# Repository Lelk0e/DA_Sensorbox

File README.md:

# DA_Sensorbox
Partnerfirma: b2-electronics
Teammitglieder: Mayer Phillip, Yilmaz Mert-Can, Schatzmann Alexander, Marte Linus
Software: Clockify, Github

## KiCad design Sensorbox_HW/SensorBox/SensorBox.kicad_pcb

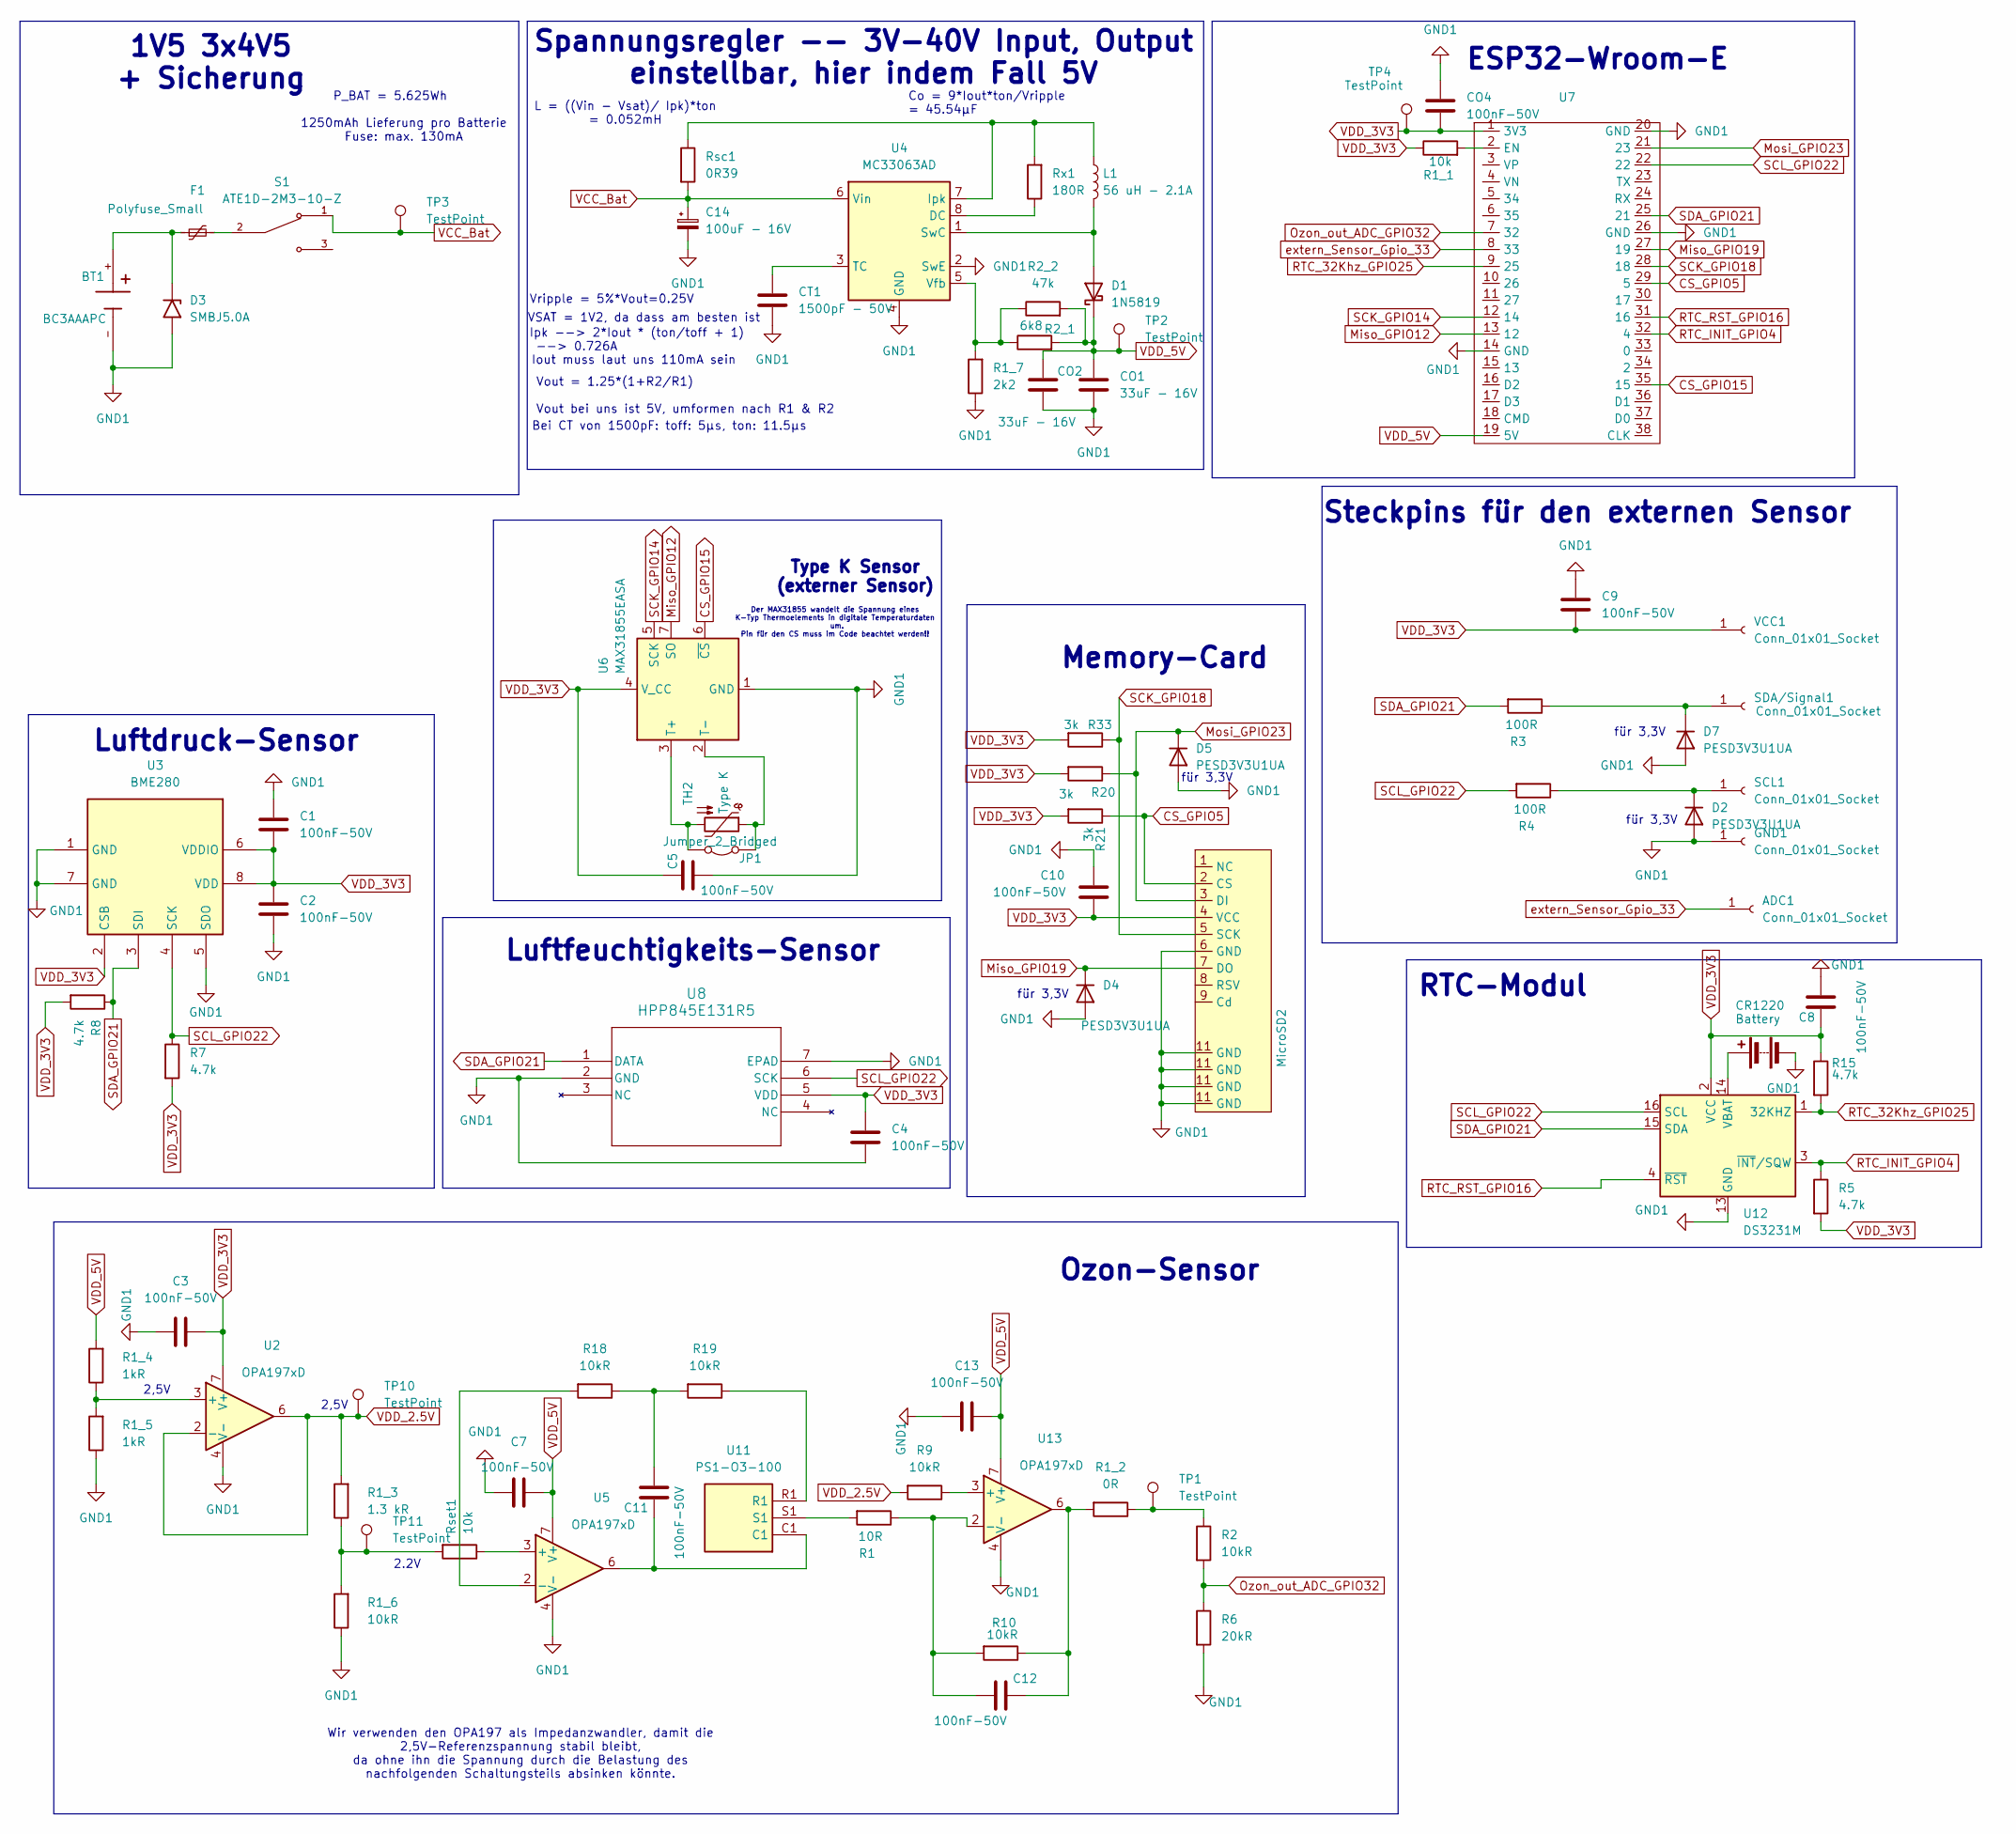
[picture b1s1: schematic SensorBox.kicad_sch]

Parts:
ADC1: Conn_01x01_Socket; PinHeader_1x01_P2.00mm_Vertical
BT1: BC3AAAPC; BatteryHolder_Keystone_2479_3xAAA; PARTREV J
C1, C2, C3, C4, C5, C7, C8, C9, C10, C11, C12, C13: 100nF-50V; C_1206_3216Metric_Pad1.33x1.80mm_HandSolder
C14: 100uF - 16V; CP_Elec_6.3x7.7
CO1, CO2: 33uF - 16V; C_1812_4532Metric_Pad1.57x3.40mm_HandSolder
CO4: 100nF-50V; C_1206_3216Metric_Pad1.33x1.80mm_HandSolder
CR1220: Battery; BatteryHolder_LINX_BAT-HLD-012-SMT
CT1: 1500pF - 50V; C_1206_3216Metric_Pad1.33x1.80mm_HandSolder
D1: 1N5819; D_SMB-SMC_Universal_Handsoldering
D2, D4, D5, D7: PESD3V3U1UA; D_SOD-323
D3: SMBJ5.0A; D_SMB_Handsoldering
F1: Polyfuse_Small; Fuse_Littelfuse_372_D8.50mm
GND1: Conn_01x01_Socket; PinHeader_1x01_P2.00mm_Vertical
JP1: Jumper_2_Bridged; PinHeader_1x02_P2.54mm_Vertical
L1: 56 uH - 2.1A; L1
MicroSD2: microSD_HC_Molex_104031-0811
R1: 10R; R_1206_3216Metric_Pad1.30x1.75mm_HandSolder
R1_1: 10k; R_1206_3216Metric_Pad1.30x1.75mm_HandSolder
R1_2: 0R; R_1206_3216Metric_Pad1.30x1.75mm_HandSolder
R1_3: 1.3 kR; R_1206_3216Metric_Pad1.30x1.75mm_HandSolder
R1_4, R1_5: 1kR; R_1206_3216Metric_Pad1.30x1.75mm_HandSolder
R1_6, R2, R9, R10, R18, R19: 10kR; R_1206_3216Metric_Pad1.30x1.75mm_HandSolder
R1_7: 2k2; R_1206_3216Metric_Pad1.30x1.75mm_HandSolder
R2_1: 6k8; R_1206_3216Metric_Pad1.30x1.75mm_HandSolder
R2_2: 47k; R_1206_3216Metric_Pad1.30x1.75mm_HandSolder
R3, R4: 100R; R_1206_3216Metric_Pad1.30x1.75mm_HandSolder
R5, R7, R8, R15: 4.7k; R_1206_3216Metric_Pad1.30x1.75mm_HandSolder
R6: 20kR; R_1206_3216Metric_Pad1.30x1.75mm_HandSolder
R20, R21, R33: 3k; R_1206_3216Metric_Pad1.30x1.75mm_HandSolder
Rsc1: 0R39; R_1206_3216Metric_Pad1.30x1.75mm_HandSolder
Rset1: 10k; R_1206_3216Metric_Pad1.30x1.75mm_HandSolder
Rx1: 180R; R_1206_3216Metric_Pad1.30x1.75mm_HandSolder
S1: ATE1D-2M3-10-Z; SW_ATE1D-2M3-10-Z
SCL1: Conn_01x01_Socket; PinHeader_1x01_P2.00mm_Vertical
SDA/Signal1: Conn_01x01_Socket; PinHeader_1x01_P2.00mm_Vertical
TH2: Type K; R_Axial_DIN0204_L3.6mm_D1.6mm_P5.08mm_Horizontal
TP1, TP2, TP3, TP4, TP10, TP11: TestPoint; TestPoint_Loop_D1.80mm_Drill1.0mm_Beaded
U2, U5, U13: OPA197xD; SOIC-8_3.9x4.9mm_P1.27mm
U3: BME280; Bosch_LGA-8_2.5x2.5mm_P0.65mm_ClockwisePinNumbering_ch
U4: MC33063AD; SOIC-8_3.9x4.9mm_P1.27mm
U6: MAX31855EASA; SOIC-8_3.9x4.9mm_P1.27mm
U7: ESP32_Wroom_E
U8: HPP845E131R5; SON6_HPP845E131R5_TEC
U11: PS1-O3-100; PS1O3100; Manufacturer_Part_Number PS1-O3-100
U12: DS3231M; SOIC-16W_7.5x10.3mm_P1.27mm
VCC1: Conn_01x01_Socket; PinHeader_1x01_P2.00mm_Vertical

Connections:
CS_GPIO5: MicroSD2.2 (CS), R21.1, U7.29 (5)
CS_GPIO15: U6.6 (~CS), U7.35 (15)
GND1: BT1.-, C1.1, C2.1, C3.2, C4.2, C5.2, C7.2, C8.2, C9.2, C10.2, C13.2, C14.2, CO1.2, CO2.2, CO4.1, CR1220.2 (-), CT1.2, D2.2 (A), D3.2 (A2), D4.2 (A), D5.2 (A), D7.2 (A), GND1.1, MicroSD2.6 (GND), MicroSD2.11 (GND), R1_5.1, R1_6.1, R1_7.1, R6.2, U2.4 (V-), U3.1 (GND), U3.5 (SDO), U3.7 (GND), U4.2 (SwE), U4.4 (GND), U5.4 (V-), U6.1 (GND), U7.14 (GND), U7.20 (GND), U7.26 (GND), U8.2 (GND), U8.7 (EPAD), U12.5 (GND), U12.6 (GND), U12.7 (GND), U12.8 (GND), U12.9 (GND), U12.10 (GND), U12.11 (GND), U12.12 (GND), U12.13 (GND), U13.4 (V-)
Miso_GPIO12: U6.7 (SO), U7.13 (12)
Miso_GPIO19: D4.1 (K), MicroSD2.7 (DO), U7.27 (19)
Mosi_GPIO23: D5.1 (K), MicroSD2.3 (DI), R20.1, U7.21 (23)
unnamed: C11.1, U5.6, U11.C1
unnamed: C11.2, R18.1, R19.2
unnamed: C12.2, R1_2.2, R10.1, U13.6
unnamed: CR1220.1 (+), U12.14 (VBAT)
unnamed: D1.2 (A), L1.2, U4.1 (SwC)
unnamed: D2.1 (K), R4.1, SCL1.1
unnamed: BT1.+, D3.1 (A1), F1.1
unnamed: D7.1 (K), R3.1, SDA/Signal1.1
unnamed: F1.2, S1.2
unnamed: JP1.1 (A), TH2.1, U6.2 (T-)
unnamed: JP1.2 (B), TH2.2, U6.3 (T+)
unnamed: R1.2, U11.S1
unnamed: R1_2.1, R2.1, TP1.1
unnamed: R1_3.1, R1_6.2, Rset1.2, TP11.1
unnamed: R19.1, U11.R1
unnamed: R1_4.1, R1_5.2, U2.3 (+)
unnamed: Rx1.1, U4.8 (DC)
unnamed: L1.1, Rsc1.1, Rx1.2, U4.7 (Ipk)
unnamed: CT1.1, U4.3 (TC)
unnamed: R1_7.2, R2_1.1, R2_2.1, U4.5 (Vfb)
unnamed: Rset1.1, U5.3 (+)
unnamed: R18.2, U5.2 (-)
unnamed: R1_1.2, U7.2 (EN)
unnamed: R9.1, U13.3 (+)
unnamed: C12.1, R1.1, R10.2, U13.2 (-)
Ozon_out_ADC_GPIO32: R2.2, R6.1, U7.7 (32)
RTC_32Khz_GPIO25: R15.2, U7.9 (25), U12.1 (32KHZ)
RTC_INIT_GPIO4: R5.1, U7.32 (4), U12.3 (~INT/SQW)
RTC_RST_GPIO16: U7.31 (16), U12.4 (~RST)
SCK_GPIO14: U6.5 (SCK), U7.12 (14)
SCK_GPIO18: MicroSD2.5 (SCK), R33.1, U7.28 (18)
SCL_GPIO22: R4.2, R7.1, U3.4 (SCK), U7.22, U8.6 (SCK), U12.16 (SCL)
SDA_GPIO21: R3.2, R8.1, U3.3 (SDI), U7.25 (21), U8.1 (DATA), U12.15 (SDA)
VCC_Bat: C14.1, Rsc1.2, S1.1, TP3.1, U4.6 (Vin)
VDD_2.5V: R1_3.2, R9.2, TP10.1, U2.2 (-), U2.6
VDD_3V3: C1.2, C2.2, C3.1, C4.1, C5.1, C8.1, C9.1, C10.1, CO4.2, MicroSD2.4 (VCC), R1_1.1, R5.2, R7.2, R8.2, R15.1, R20.2, R21.2, R33.2, TP4.1, U2.7 (V+), U3.2 (CSB), U3.6 (VDDIO), U3.8 (VDD), U6.4 (V_CC), U7.1 (3V3), U8.5 (VDD), U12.2 (VCC), VCC1.1
VDD_5V: C7.1, C13.1, CO1.1, CO2.1, D1.1 (K), R1_4.2, R2_1.2, R2_2.2, TP2.1, U5.7 (V+), U7.19 (5V), U13.7 (V+)
extern_Sensor_Gpio_33: ADC1.1, U7.8 (33)

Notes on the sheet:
für 3,3V
Luftdruck-Sensor
Vripple = 5%*Vout=0.25V
Spannungsregler -- 3V-40V Input, Output einstellbar, hier indem Fall 5V
Luftfeuchtigkeits-Sensor
Ipk --> 2*Iout * (ton/toff + 1) --> 0.726A
Type K Sensor (externer Sensor)
Steckpins für den externen Sensor
1V5 3x4V5 + Sicherung
Memory-Card
Bei CT von 1500pF: toff: 5µs, ton: 11.5µs
Iout muss laut uns 110mA sein
ESP32-Wroom-E
Der MAX31855 wandelt die Spannung eines K-Typ Thermoelements in digitale Temperaturdaten um. Pin für den CS muss im Code beachtet werden!!
RTC-Modul
Wir verwenden den OPA197 als Impedanzwandler, damit die 2,5V-Referenzspannung stabil bleibt, da ohne ihn die Spannung durch die Belastung des nachfolgenden Schaltungsteils absinken könnte.
VSAT = 1V2, da dass am besten ist
1250mAh Lieferung pro Batterie Fuse: max. 130mA
Co = 9*Iout*ton/Vripple = 45.54µF
Vout = 1.25*(1+R2/R1) Vout bei uns ist 5V, umformen nach R1 & R2
P_BAT = 5.625Wh
L = ((Vin - Vsat)/ Ipk)*ton = 0.052mH
2,5V
Ozon-Sensor
2.2V

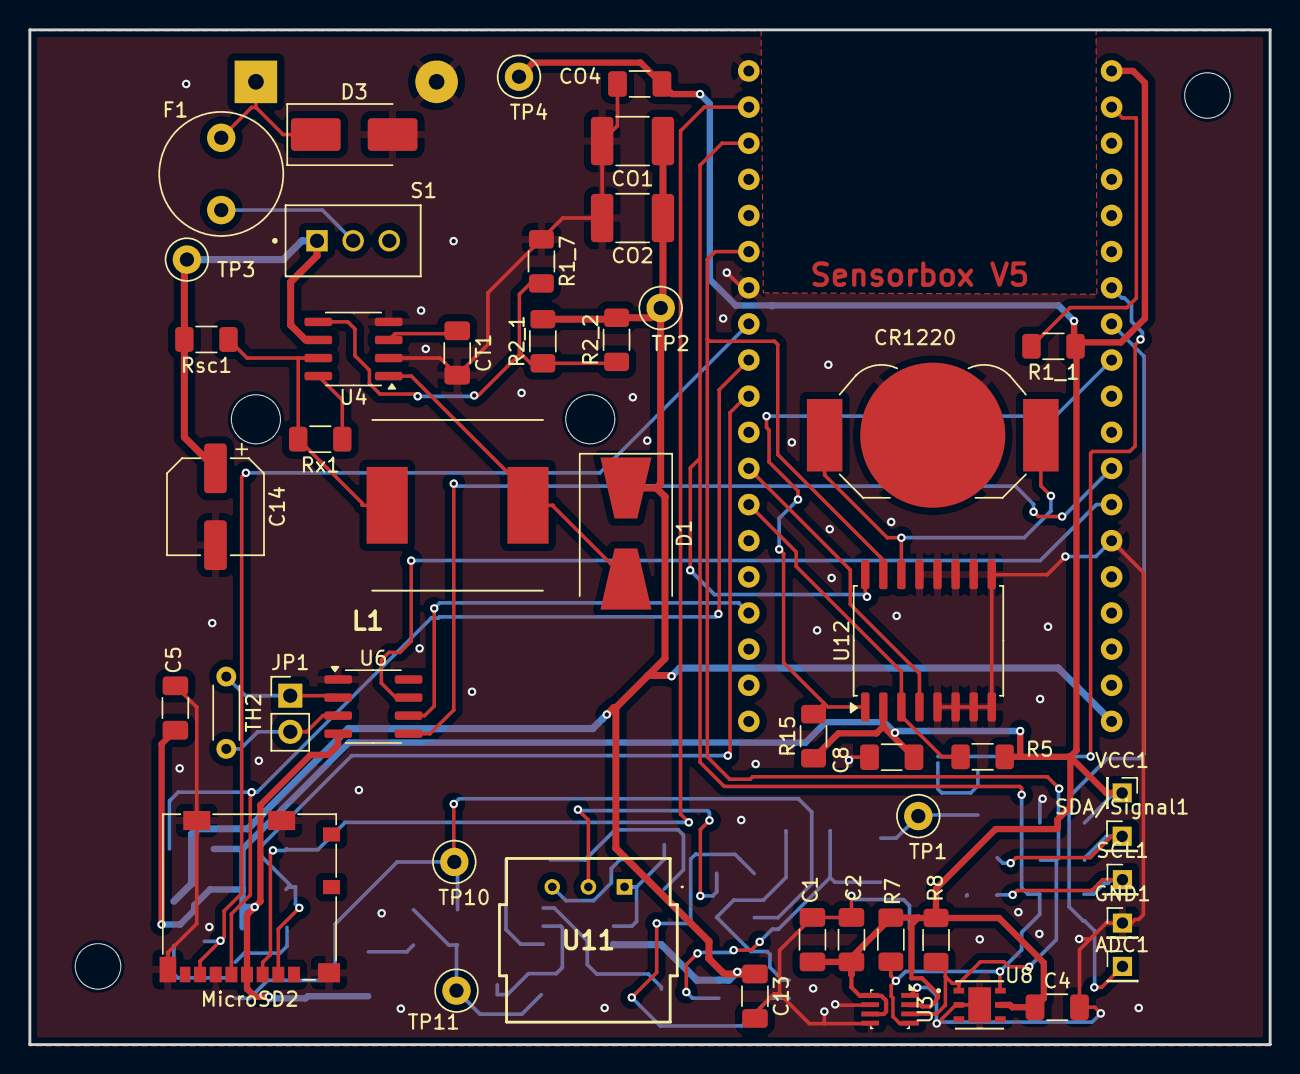
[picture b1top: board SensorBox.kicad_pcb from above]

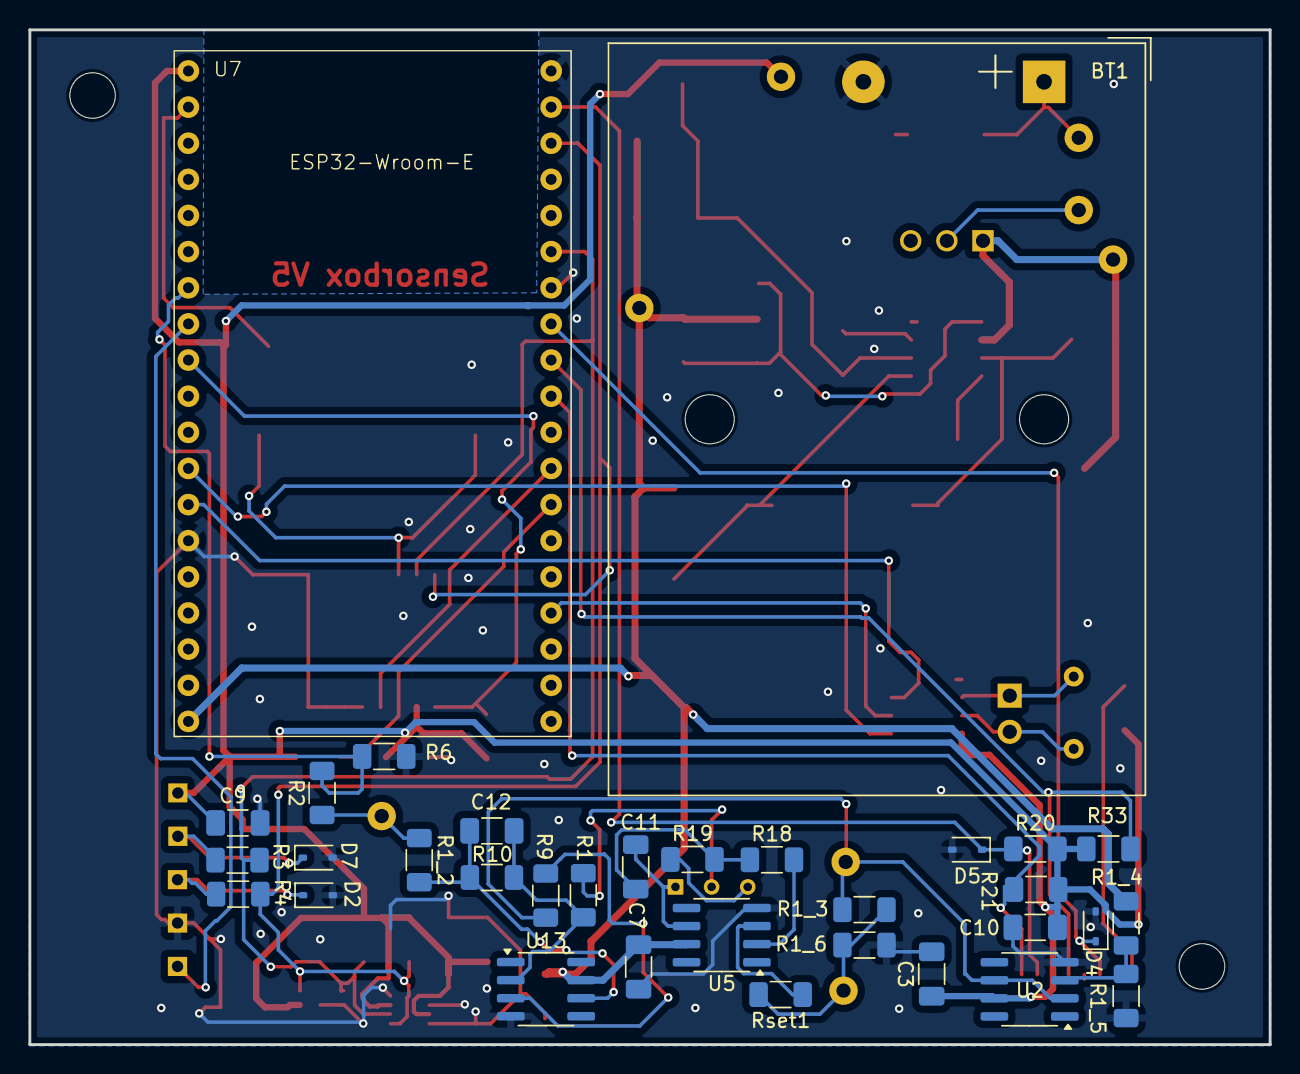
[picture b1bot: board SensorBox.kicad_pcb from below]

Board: 2 copper layers, 87.2 x 71.3 mm, 80 parts (33 on the bottom side), 44 nets.

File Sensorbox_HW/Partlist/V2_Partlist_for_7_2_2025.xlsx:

HW-SENSORBOX
Bauteilnamen | Werte | Datasheet | Footprint | Anzahl für 1 Sensorbox | Anzahl für 4 Sensorboxen | Bestellnummer | Besteller | Link
ADC1,GND1,SCL1,SDA/Signal1,VCC1 | Conn_01x01_Socket | ~ | Connector_PinHeader_2.00mm:PinHeader_1x01_P2.00mm_Vertical | 5 | 10 | BCS-105-L-S-TE | Mouser | https://www.mouser.at/ProductDetail/Samtec/BCS-105-L-S-TE?qs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
BT1 | BC3AAAPC |  | Battery_Basket:BatteryHolder_Keystone_2479_3xAAA | 1 | 10 | BC4AAAPC-ND | Digikey | https://www.digikey.com/en/products/detail/mpd-memory-protec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
C1,C2,C3,C4,C5,C7,C8,C9,C10,C11,C12,C13,CO4 | 100nF-50V | ~ | Capacitor_SMD:C_1206_3216Metric_Pad1.33x1.80mm_HandSolder | 13 | 130 | VJ1206Y104JXAAT | Mouser | https://www.mouser.at/ProductDetail/Vishay-Vitramon/VJ1206Y1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
C14 - GEPOLT | 100uF - 16V | ~ | Capacitor_SMD:CP_Elec_6.3x7.7 | 1 | 10 | AVS107M16E16T-F | Mouser | https://www.mouser.at/ProductDetail/Cornell-Dubilier-CDE/AVS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
CO1,CO2 | 33uF - 16V | ~ | Capacitor_SMD:C_1812_4532Metric_Pad1.57x3.40mm_HandSolder | 2 | 20 | C4532X5R1C336M250KA | Mouser | https://www.mouser.at/ProductDetail/TDK/C4532X5R1C336M250KA?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
CR1220 | Battery | ~ | Battery:BatteryHolder_LINX_BAT-HLD-012-SMT | 1 | 10 | BAT-HLD-012-SMT | Mouser | https://eu.mouser.com/ProductDetail/TE-Connectivity-Linx-Tec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
CT1 | 1500pF - 50V | ~ | Capacitor_SMD:C_1206_3216Metric_Pad1.33x1.80mm_HandSolder | 1 | 10 | VJ1206A152JXAMT | Mouser | https://www.mouser.at/ProductDetail/Vishay-Vitramon/VJ1206A1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
D1 | 1N5819 | http://www.vishay.com/docs/88525/1n5817.pdf | Diode_SMD:D_SMB-SMC_Universal_Handsoldering | 1 | 10 | 1N5819HW-7-F | Mouser | https://www.mouser.at/ProductDetail/Diodes-Incorporated/1N58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
D2,D4,D5,D7 | PESD3V3U1UA | https://www.vishay.com/docs/85751/1n4148ws.pdf | Diode_SMD:D_SOD-323 | 4 | 40 | PESD3V3U1UA,115 | Mouser | https://www.mouser.at/ProductDetail/Nexperia/PESD3V3U1UA115?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
D3 | SMBJ5.0A | https://www.vishay.com/docs/88301/15ke.pdf | Diode_SMD:D_SMB_Handsoldering | 1 | 10 | SMBJ5.0A-E3/52 | Mouser | https://www.mouser.at/ProductDetail/Vishay-General-Semicondu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
F1 | Polyfuse_Small | ~ | Fuse:Fuse_Littelfuse_372_D8.50mm | 1 | 10 | LVR016K | Mouser | https://www.mouser.at/ProductDetail/Littelfuse/LVR016K?qs=sG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
JP1 | Jumper_2_Bridged | ~ | Connector_PinHeader_2.54mm:PinHeader_1x02_P2.54mm_Vertical | 1 | 10 | 61300211121 | Mouser | https://www.mouser.at/ProductDetail/Wurth-Elektronik/6130021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
L1 | 56ÂµH - 2.1A | ~ | Inductor_SMD:L_0805_2012Metric_Pad1.05x1.20mm_HandSolder | 1 | 10 | 744771156 | Mouser | https://www.mouser.at/ProductDetail/Wurth-Elektronik/7447711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
MicroSD2,U7 | ~ |  | -- mixed values -- | 2 | 10 | 104031-0811 | Mouser | https://www.mouser.at/ProductDetail/Molex/104031-0811?qs=uds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
R1 | 10R | ~ | Resistor_SMD:R_1206_3216Metric_Pad1.30x1.75mm_HandSolder | 1 | 10 | TNPW120610R0BEEA | Mouser | https://www.mouser.at/ProductDetail/Vishay-Dale/TNPW120610R0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
R1_1,Rset1 | 10k | ~ | Resistor_SMD:R_1206_3216Metric_Pad1.30x1.75mm_HandSolder | 2 | 20 | RT1206FRE1310KL | Mouser | https://www.mouser.at/ProductDetail/YAGEO/RT1206FRE1310KL?qs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
R1_2 | 0R | ~ | Resistor_SMD:R_1206_3216Metric_Pad1.30x1.75mm_HandSolder | 1 | 10 | MCA12060Z0000ZP500 | Mouser | https://www.mouser.at/ProductDetail/Vishay-Beyschlag/MCA1206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
R1_3 | 1.3 kR | ~ | Resistor_SMD:R_1206_3216Metric_Pad1.30x1.75mm_HandSolder | 1 | 10 | CRCW12061K30FKEAHP | Mouser | https://www.mouser.at/ProductDetail/Vishay-Dale/CRCW12061K30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
R1_4,R1_5 | 1kR | ~ | Resistor_SMD:R_1206_3216Metric_Pad1.30x1.75mm_HandSolder | 2 | 20 | ERA-8AEB102V | Mouser | https://www.mouser.at/ProductDetail/Panasonic/ERA-8AEB102V?q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
R1_6,R2,R9,R10,R18,R19 | 10kR | ~ | Resistor_SMD:R_1206_3216Metric_Pad1.30x1.75mm_HandSolder | 6 | 60 | ERA-8VRB1002V | Mouser | https://www.mouser.at/ProductDetail/Panasonic/ERA-8VRB1002V?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
R1_7 | 2k2 | ~ | Resistor_SMD:R_1206_3216Metric_Pad1.30x1.75mm_HandSolder | 1 | 10 | ERJ-T08J222V | Mouser | https://www.mouser.at/ProductDetail/Panasonic/ERJ-T08J222V?q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
R2_1 | 6k8 | ~ | Resistor_SMD:R_1206_3216Metric_Pad1.30x1.75mm_HandSolder | 1 | 10 | MCA12060D6801BP500 | Mouser | https://www.mouser.at/ProductDetail/Vishay-Beyschlag/MCA1206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
R3,R4 | 100R | ~ | Resistor_SMD:R_1206_3216Metric_Pad1.30x1.75mm_HandSolder | 2 | 20 | RT1206FRE13100RL | Mouser | https://www.mouser.at/ProductDetail/YAGEO/RT1206FRE13100RL?q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
R5,R7,R8,R15 | 4.7k | ~ | Resistor_SMD:R_1206_3216Metric_Pad1.30x1.75mm_HandSolder | 4 | 40 | RT1206FRE074K7L | Mouser | https://www.mouser.at/ProductDetail/YAGEO/RT1206FRE074K7L?qs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
R6 | 20kR | ~ | Resistor_SMD:R_1206_3216Metric_Pad1.30x1.75mm_HandSolder | 1 | 10 | ERA-8APB203V | Mouser | https://www.mouser.at/ProductDetail/Panasonic/ERA-8APB203V?q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
R20,R21,R33 | 3k | ~ | Resistor_SMD:R_1206_3216Metric_Pad1.30x1.75mm_HandSolder | 3 | 30 | RT1206FRE073KL | Mouser | https://www.mouser.at/ProductDetail/YAGEO/RT1206FRE073KL?qs=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
Rsc1 | 0R39 | ~ | Resistor_SMD:R_1206_3216Metric_Pad1.30x1.75mm_HandSolder | 1 | 10 | RCWE1206R390FKEA | Mouser | https://www.mouser.at/ProductDetail/Vishay-Dale/RCWE1206R390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
Rx1 | 180R | ~ | Resistor_SMD:R_1206_3216Metric_Pad1.30x1.75mm_HandSolder | 1 | 10 | TNPW1206180RBEEA | Mouser | https://www.mouser.at/ProductDetail/Vishay-Dale/TNPW1206180R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
TH2 | Type K | https://www.heraeus.com/media/media/group/doc_group/products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 | Resistor_THT:R_Axial_DIN0204_L3.6mm_D1.6mm_P5.08mm_Horizontal | 0 | 0 | Type K, PTFE, 1m | x | x
TP1,TP2,TP3,TP4,TP5,TP6,TP7,TP10,TP11 | TestPoint | ~ | TestPoint:TestPoint_Loop_D1.80mm_Drill1.0mm_Beaded | 9 | 100 | SMC-1-01-1-GT | Digikey | https://www.digikey.com/en/products/detail/adam-tech/SMC-1-0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
U1 | BME280 | https://www.bosch-sensortec.com/media/boschsensortec/downloa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 | BME280 (2):BME280 | 0 | 0 | x | x | x
U2,U5,U13 | OPA197xD | http://www.ti.com/lit/ds/symlink/opa197.pdf | Package_SO:SOIC-8_3.9x4.9mm_P1.27mm | 3 | 30 | OPA197IDR | Mouser | https://www.mouser.at/ProductDetail/Texas-Instruments/OPA197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
U4 | MC33063AD | http://www.onsemi.com/pub_link/Collateral/MC34063A-D.PDF | Package_SO:SOIC-8_3.9x4.9mm_P1.27mm | 0 | 0 | x | x | x
U6 | MAX31855EASA | http://datasheets.maximintegrated.com/en/ds/MAX31855.pdf | Package_SO:SOIC-8_3.9x4.9mm_P1.27mm | 1 | 10 | MAX31855EASA+ | Mouser | https://www.mouser.at/ProductDetail/Analog-Devices-Maxim-Int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
U8 | HPP845E131R5 | HPP845E131R5 | HPP_footprints:SON6_HPP845E131R5_TEC | 0 | 0 | x | x | x
U11 | PS1-O3-100 | https://sgx.cdistore.com/datasheets/sgx/ds-0353-ps1ps4-o3-100.pdf | Ozonsensor:PS1O3100 | 0 | 0 | x | x | x
U12 | DS3231M | http://datasheets.maximintegrated.com/en/ds/DS3231.pdf | Package_SO:SOIC-16W_7.5x10.3mm_P1.27mm | 1 | 10 | DS3231M+ | Mouser | https://www.mouser.at/ProductDetail/Analog-Devices-Maxim-Int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
Jumper | x | x | x | 1 | 10 | M7686-05 | Mouser | https://www.mouser.at/ProductDetail/Harwin/M7686-05?qs=%252B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
2x 19pin für esp | x | x | x | 2 | 20 | SSW-119-01-T-S | Mouser | https://www.mouser.at/ProductDetail/Samtec/SSW-119-01-T-S?qs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
5pin Stecker ex.Sensor | x | x | x | 1 | 10 | 61300511121 | Mouser | https://www.mouser.at/ProductDetail/Wurth-Elektronik/6130051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
2 pin Socket (für TypK-Sensor) | x | x | x | 1 | 10 | SMC-1-02-1-GT | Mouser | https://www.mouser.at/ProductDetail/Adam-Tech/SMC-1-02-1-GT?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
CR1220 Batterie | x | https://www.mouser.at/datasheet/2/575/1/2684410000_BATTERY_C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 | x | 1 | 10 | 2684410000 | Mouser | https://www.mouser.at/ProductDetail/Weidmuller/2684410000?qs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

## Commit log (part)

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2024-07-20 lastenheft
2024-07-29 Pflichtenheft v1.1
    Pflichtenheft überarbeitet
2024-08-04 push
2024-09-17 änderung beim pflichtenheft software
2024-09-23 ESP32-Wroom-32e Datasheet push
2024-09-30 Pflichtenheft-Finale
2024-09-30 Sensorik
    4 sensoren
2024-10-07 Sensorik_final
    bearbeitet und finalisiert
2024-10-21 Schaltplan_Sensorbox
    Projekt für den Schaltplan erstellen
2024-10-21 Schaltpläne
    Einzelne Schaltpläne (Layouts) eingefügt
2024-10-21 schalt
    fehler bei sch. dateien --> versucht zu fixen
2024-10-21 sch
    namen geändert von dateien
2024-10-30 big change - hardware
    folders changed, new proj. assigned
2024-10-30 name changed of sensorbox
2024-10-31 Hauptschaltung
    Sensorbox, erste Hauptschaltung realisiert --> ESP32 C6 selbst designt und eingebaut und die restlichen Funktionen eingebaut --> SD Karte mit ESP verbunden, Spannungsregler eingebaut für die Spannung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
2024-11-01 Main Sensor-Schaltung Revision 2
2024-11-18 schaltplan änderungen
    spannungswandler und pins geändert
2024-12-02 Testing sending data from multiple sensors with a wifi sleep
2024-12-11 Mesh Topology, measure power consumption
    Wir haben uns die Mesh Topologie vertieft angeschaut, wobei wir uns gedacht haben zuerst eine kurze Verbindung zum Router zu erstellen um eine API anfrage für den Referenzdruck rauszusenden. Weiter h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
2024-12-14 Schaltplan
    Schematic changed, fixes to hpp sensor and to the convertor. In addition changes to voltage supply
2024-12-16 schaltplan update
    batterie getauscht
2024-12-26 Batterie und Regler
    eingestellt und berechnet
2024-12-27 änderungen
    50h gecheckt, bme angepasst
    bme und hpp beschriftet
    Eingang und Ausgang leitungen angepasst nach draußen oder nach innen
2024-12-28 SD_CARD_Modul
    Library für SD Karte Modul
2024-12-28 Lib
    library erschaffen bezüglich dem sd modul zum ablesen und schreiben
    plus im hauptschaltplan eingesetzt
2024-12-28 Library
    Library ESP
2024-12-28 Erweiterung V3
    Library für den ESP32 Wroom E erstellt, die Verbindungen ausgetauscht vom C6 zum neuen ESP und die SD Karte verbunden
2024-12-28 Asynchrones Hosting recherche
    Research associated to asynchrony hosting
    --> what is it? how does it work? what is the difference between synchrony hosting?
    In addition there are several applications, which can run on this format.
    On the other hand, most of the asyn. programs are in C written and the http environment is implemented with js.
    My Opinion:
    The implementation of the asyn. programs is quite difficult and complex, but will be further analyzed. A few general aspects of asyn. is already known and the base function of it, is also not so comp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
2024-12-29 SensorboxV3
    Ozonsensor eingebaut mit schaltung, Inverter Eingebaut für Ozonsensor-Schaltung
2024-12-30 async Webserver erstellt
    Ich habe einen Asynchronen Webserver erstellt der es ermöglichen soll eine Webpage zu hosten die, die Sensordaten darstellt
2024-12-30 Revert "changes"
    This reverts commit 985babfc8de051d71098531e7ef970764ba211a7.
2024-12-30 change code
    A few errors were fixed, but there are still some existing, like http request is not working or there are some other unknown errors.
    i tried to fix but was not able to fix them.
2025-01-01 Überarbeitung
2025-01-02 RTC-Modul einbauen
    Das RTC Modul eingebaut und die doku geschrieben
2025-01-02 html canvas (graph) x axe changes
    i updated the graph today. There are several changes. First there is a reset command for the graph, so the graph can have a reset, when the function (e.g. canvas_setting()) is being applied. But it d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
    Further more, the time zones were set, meaning, the graph can set his x axe to hours, days. This means our graph can show the user pieces of information of our sensor from a whole year.
2025-01-04 Update namedMesh_AsyncWebserver_filesystem.ino
    Den Webserver erweitert mit dem Filesystem und den Code besser Lesbar zu machen
2025-01-11 Sensorbox V3
    RTC-Modul selber gebaut, Micro-SD-Karte gebaut, Alles angeordnet, Pullup-Widerstände hinzugefügt
2025-01-13 Überarbeitung Sensorbox V3
    Sicherheitsschaltung eingebaut, ESP anschauen warum getauscht, Email geschrieben
2025-01-16 bug fix of the graph (x-axe)
    It is a small change, but an important change. I fixed the appearance of double symbols when changing the time zone, like from "today" to "this month", etc. The symbols were overlapping, which should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
    A small reminder, the whole program, is written in a format, so that it can automatically adjust to the screen size. But of course, i did not test that yet, i have to test it someday. Theoretically (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
2025-01-16 Überarbeitung V3
    Besprechung mit B2 und einige Dinge Überarbeitet (Fuse, SD Card usw.)
2025-01-20 test
    test
2025-01-25 Präsentation
    Präsentation
2025-01-30 docu
    A small amount of documentation was done by me, specifically the website documentation. I edited a small, there is still much work to do.
2025-02-03 rtc-module & sd-module
    I changed the directionary folders of these modules.
2025-02-03 changes hw
    problems with sch.
2025-02-03 PCB
    Footprints zuweisen
2025-02-05 Sensorbox
    Layout erstellt
2025-02-05 ddd
    dddd
2025-02-07 Besprechung
    Besprechung B2 Layout
2025-02-07 PCB überarbeitung
2025-02-10 changes website
    Ich habe ein paar test-Daten damals hochgeladen, jedoch werden diese derzeit nicht benutzt.
2025-02-10 expanded low power mode, error correction, added ssl not working yet
    Low Power Mode so ausgearbeitet dass er nur durch ein Signal von der MainBox eingeschaltet werden kann. Des weiteren wurde der Server mit https erweitert was bis jetzt noch nicht fehlerfrei funktioni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
2025-02-11 finished LPM, added writing DB data to webserver
    Der LPM wurde fertiggestellt so dass er synchron mit den anderen ESP´s funktioniert. Eine Methode zum senden der Daten an den Webserver wurde erstellt. LPM wird mit dem Taskscheduler gehandelt für sy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
2025-02-11 fetch data vom BME
    Es wurde versucht mithilfe einer asyn. fetch methode, Daten abzulesen (in dem Format, was gewollt war), die Methode wurde so geschrieben, dass diese wiederum für die anderen Sensoren benutzt werden k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
2025-02-12 Stückliste nochmal überbearbeitet
    Da die Stückliste noch ein paar fehlerhafte Batterie Typen hatte (CR1220), hab diesen nochmal gefixt. Dazu hat ein Link nicht richtig funktioniert, dieser wurde ebenfalls gefixt.
2025-02-16 fixed errors in sqlite and in initializing
    sqlite hat standard c File-Operations benutzt anstatt von der SD-Karte. PinOut hat sich geändert
2025-02-16 Doku V3
    Die Dokumentation bezüglich der 3.Version von der Hardware wurde geschrieben.
2025-02-17 website sending request
    Sende Anfrage (Code) wurde basierend auf wlan/asynch. geschrieben.
2025-02-17 Doku weiterarbeiten
    Version 4 schreiben
2025-02-21 Changes Website and test sending
    Die Zeitanzeige der Website wurde geändert --> Jahresanzeigen oder Monatsanzeigen wurden als unnötig bewertet. Stattdessen wurden 1h, 2Tage und 2Wochen Ansicht eingebaut.
    Um diesen Code zu testen, wurde eine Extension in VsCode gefunden, welcher die Codezeilen viel simpler macht, als wenn man es in Arduino schreiben würde. Diese Extension ist wichtig, damit man die Da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
2025-02-23 fixed and updated logging
    Die logging Funktion wurde so angepasst das sie auch mitten in der Messung abgebrochen werden kann und auch wieder zurückgesetzt werden kann.
2025-02-24 http host
    Der Code basierd auf HTTP-Host library.
2025-02-24 doc update --> inhaltsverzeichnis
2025-02-26 Reworked SQlite in MainESP for better Timestamping
    Jahr, Monat und Tag hinzugefügt um Timestamps zu verbessern. SQlite so überarbeitet das die Datei nicht corrupted --> Datei muss Finalized werden. Code verschönert --> Übersicht
2025-02-28 Zip Datei für Testversion erstellt
    .
2025-03-01 Daten von BME mithilfe von einem WebServer erhalten
    Der Code wurde mithilfe eines XAAMP Webservers getestet. Die Time and data des bme, wurden erfolgreich angezeigt. Zusätzlich wurde statt, \n für die Sende-Datan, @ benutzt, da es einfacher ist, diese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
2025-03-02 added RTC function, reworked timestamp handling and reworked sendDB
    RTC Funktionen zum Code zugefügt aus der RTCLib von Adafruit. Timestamps so überarbeitet das sie mit dem RTC funktionieren. sendDB so überarbeitet das es nur die neuste Nachricht nach dem Timestamp a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
2025-03-04 website anpassen gemäß ESP
    Beim Code wurde die fetch adresse des bmes gemäß esp32 angepasst.
    Zusätzlich wurde ein on/off button implementiert, für den Start und Stop der Messung.
2025-03-04 fetchuserinfo änderungen
    Der Code wurde allgemein dargestellt und leserlicher hingeschrieben.
    Zusätzlich, können jetzt die anderen Sensoren die Methode benutzen.
2025-03-06 Layout
    Layout komplett neugemacht (Sensoren usw. besser platziert.)
2025-03-06 Schalter2-Änderungen
    Schalter zwischen 2 GPIOs hinzugefügt
2025-03-08 fixed guru meditation error and added more error proofing
    Der Guru Meditation error kam von der Fehlerhaften Inkludierung von AdafruitBusIO in der HTU Bibliothek anstatt in der .ini File was interne Library Fehler verursacht hat. Ein null pointer error war 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
2025-03-10 added typK sensor
    Den typk Sensor hinzugefügt und globale Pins defined. gemessene Werte plausibel.
2025-03-10 Ozon Pin zum ESP geändert
2025-03-10 added readOzon
    muss noch für Werte angepasst werden. Doku Punkte dazugeschrieben
2025-03-11 neue Test-Daten
    Die anderen Test-Daten von ozon, hpp und temp wurden geschrieben. Der Code zum lesen und zum Darstellen idieser Daten ist ähnlich wie der von dem BME.
2025-03-12 Bugs fix gestartet
    Bug fixes haben was mit dem Translate Point zu tun, bzw. mit was anderem was noch untersucht werden muss.
2025-03-13 Graph Darstellung
    Bug Fixung des Graphen. Ozon-y-achse darstellung gemacht.
2025-03-14 Update DA_Sensorbox_VORLAGE_2024_ET.docx
    Mesh dokumentiert
2025-03-14 Zeitdarstellung [stunden] bei den aktuellen simulierten Messdaten
    Die Zeitstellung basiert derzeit auf Stunden und wird noch als [min] dargestellt. Zusätzlich ist die Genauigkeit dieser Darstellung ziemlich genau und weicht garnicht von den Messdaten ab.
    Der Bug, der gefixt wurde, war, dass bei der for-loop, double Werte benutzt wurden, wegen dem, wurden die Daten auch unvollständig dargestellt.
2025-03-16 Änderungen Website (Kommentare, Funktionen)
    - Viele Kommentare wurden ergänzt oder schöner hingeschrieben, bzw. klarer formuliert.
    - Es wurde merhmals der Code gecheckt, ob dieser auch passt.
    - Zusätzlich wurde die Genauigkeit bei ein paar Sensor-Daten erhöht, wie z.B. vom Hpp, Ozon, Temp. Jedoch wurde dies beim BME vernachlässigt, da, gewisse Zahlen aufeinmal falsch zusammengezählt wurde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
2025-03-17 fetch_All_data inkludiert
    Diese Methode liest nur die ganzen Daten ab.
2025-03-22 added unique name over mac and added css and js loading
    Jeder ESP, außer der MainESP hat jetzt einen einzigartigen Namen über die Mac-Adresse
2025-03-31 änderung schaltplan (Anordnung)
2025-04-19 Websocket Funktionen implementiert
    Die mac Addressen wurden zu der mac-combobox hinzugefügt und die real-life daten sollten je nach mac-addresse beim Graph dargestellt werden. Dies wurde noch nicht getestet.
2025-05-17 improved Server stability
2025-06-07 Websockets angepasst
2025-06-12 HW-PCB-Change
    Die HW wurde angepasst --> Leiterbahnen wurden abgecheckt und geändert; PCB vom BME geändert; GND-Flächen angepasst
2025-06-28 Changed code to improve webserver stability
    Switched to a different approach, mesh pauses if client is connected so that webserver stability is guaranteed.
2025-06-29 Reworked client data handling
    Changed to a different approach, data is now sent in between pauses and then stored locally. Still searching for a solution to better save data between reloads.
